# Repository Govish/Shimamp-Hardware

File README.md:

# Shimamp-Hardware
 Hardware Design Files for high-efficiency shim amplifier

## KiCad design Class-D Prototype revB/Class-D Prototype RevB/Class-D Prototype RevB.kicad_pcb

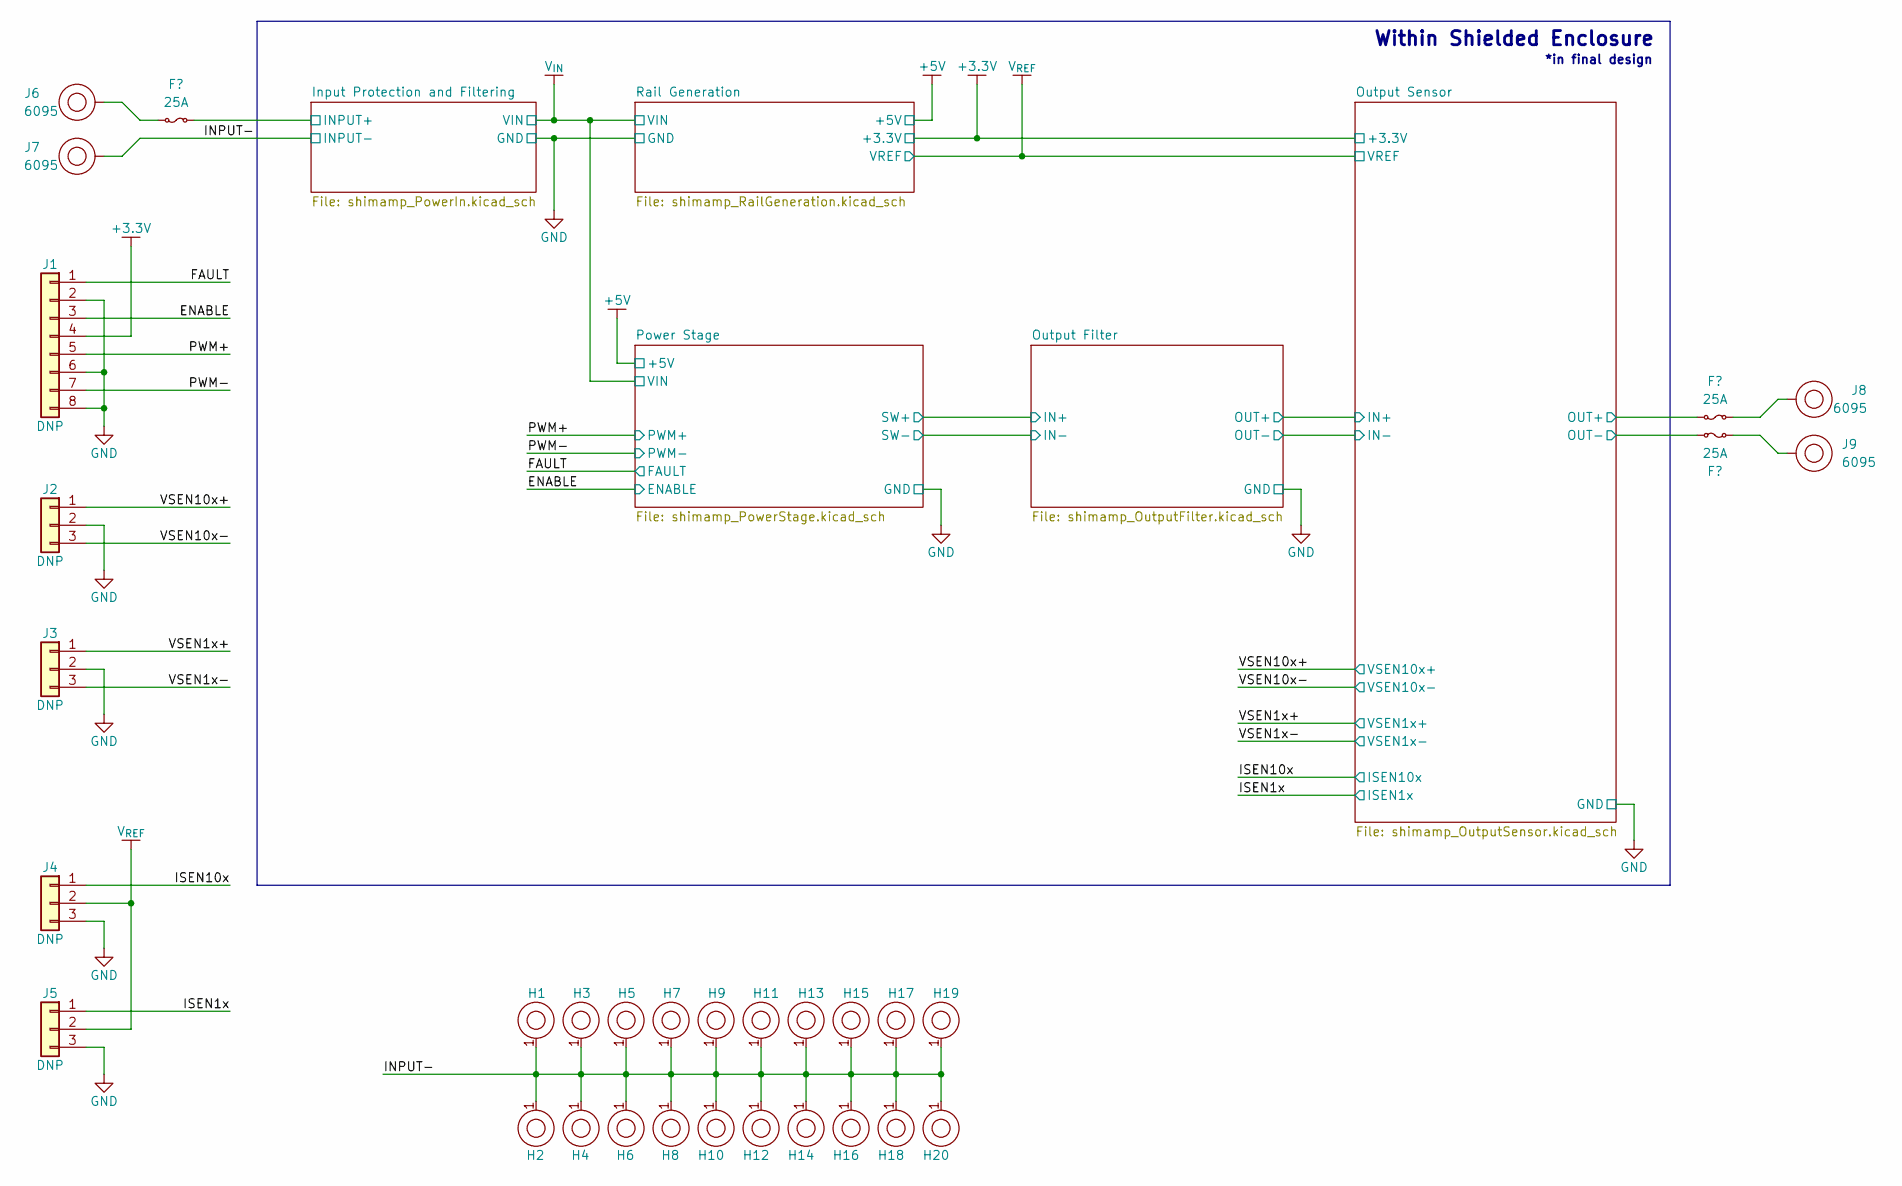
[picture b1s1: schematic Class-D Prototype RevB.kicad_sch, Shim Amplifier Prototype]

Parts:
F1, F2, F3: 25A; Fuse_1206_3216Metric_Pad1.42x1.75mm_HandSolder; Part Number 0685H9250-01
H1, H2, H3, H4, H5, H6, H7, H8, H9, H10, H11, H12, H13, H14, H15, H16, H17, H18, H19, H20: MountingHole-3mm_small_annulus
J1: DNP; PinHeader_1x08_P2.54mm_Vertical
J2, J3, J4, J5: DNP; PinHeader_1x03_P2.54mm_Vertical
J6, J7, J8, J9: 6095; Keystone 6095; Part Number 6095

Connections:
+3.3V: J1.4; also elsewhere on the board
/ENABLE: J1.3; also elsewhere on the board
/FAULT: J1.1; also elsewhere on the board
/INPUT-: H1.1, H2.1, H3.1, H4.1, H5.1, H6.1, H7.1, H8.1, H9.1, H10.1, H11.1, H12.1, H13.1, H14.1, H15.1, H16.1, H17.1, H18.1, H19.1, H20.1, J7.1; also elsewhere on the board
/ISEN1x: J5.1; also elsewhere on the board
/ISEN10x: J4.1; also elsewhere on the board
/Input Protection and Filtering/VIN_ICL+: F1.2; also elsewhere on the board
/Output Sensor/IN-: F3.1; also elsewhere on the board
/Output Sensor/OUT+: F2.1; also elsewhere on the board
/PWM+: J1.5; also elsewhere on the board
/PWM-: J1.7; also elsewhere on the board
/VSEN1x+: J3.1; also elsewhere on the board
/VSEN1x-: J3.3; also elsewhere on the board
/VSEN10x+: J2.1; also elsewhere on the board
/VSEN10x-: J2.3; also elsewhere on the board
GND: J1.2, J1.6, J1.8, J2.2, J3.2, J4.3, J5.3; also elsewhere on the board
unnamed: F1.1, J6.1
unnamed: F2.2, J8.1
unnamed: F3.2, J9.1
V_{REF}: J4.2, J5.2; also elsewhere on the board

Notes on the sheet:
*in final design
Within Shielded Enclosure

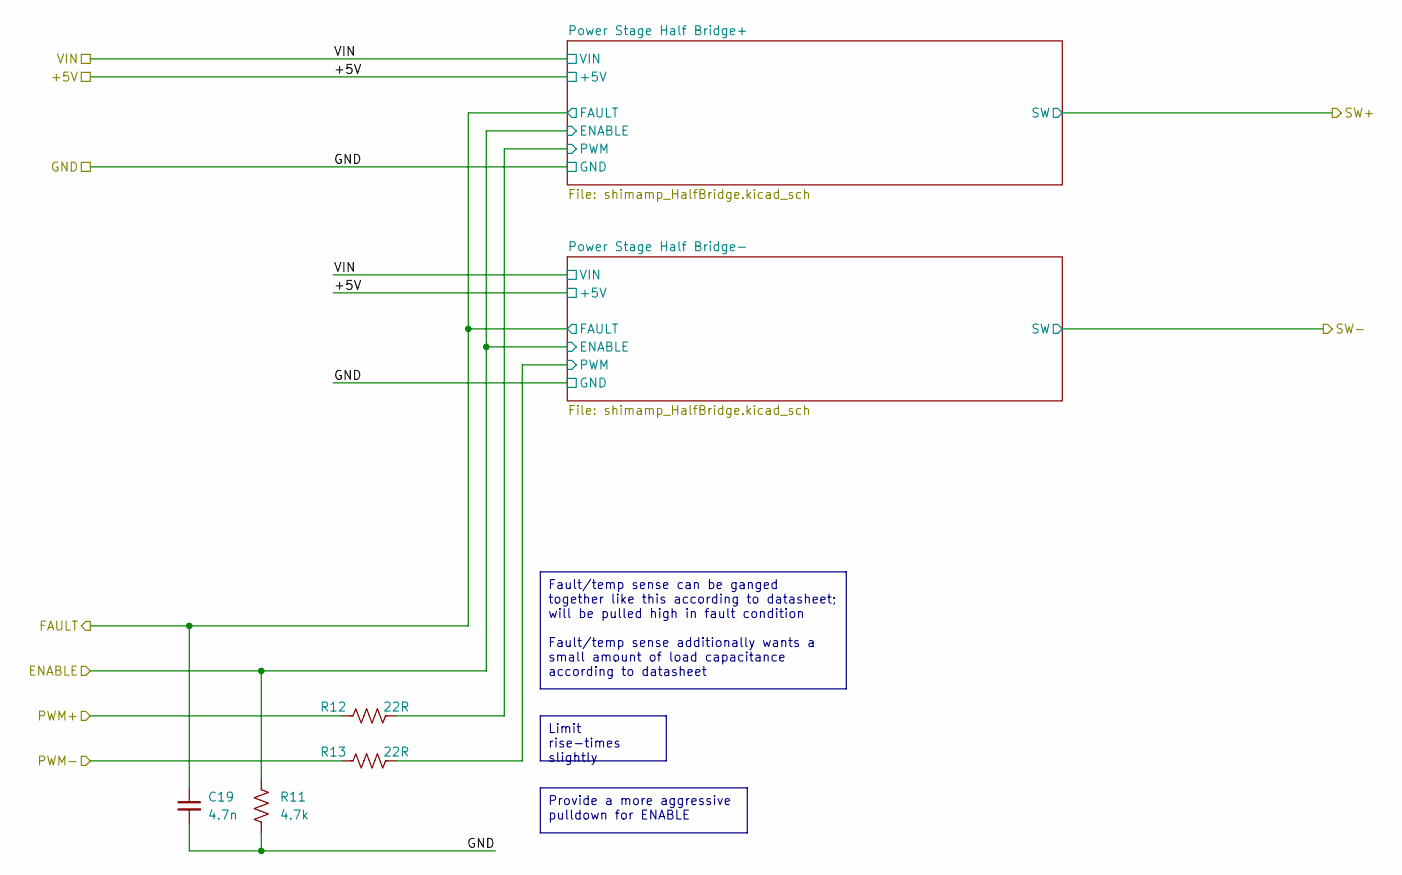
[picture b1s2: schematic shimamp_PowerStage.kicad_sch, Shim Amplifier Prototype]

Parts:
C19: 4.7n; C_0603_1608Metric_Pad1.08x0.95mm_HandSolder; Part Number CL10B472KB8NFNC
R11: 4.7k; R_0603_1608Metric_Pad0.98x0.95mm_HandSolder; Part Number RMCF0603FT4K70
R12, R13: 22R; R_0603_1608Metric_Pad0.98x0.95mm_HandSolder; Part Number RMCF0603FT22R0

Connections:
/ENABLE: R11.2; also elsewhere on the board
/FAULT: C19.1; also elsewhere on the board
/PWM+: R12.1; also elsewhere on the board
/PWM-: R13.1; also elsewhere on the board
/Power Stage/Power Stage Half Bridge+/PWM: R12.2; also elsewhere on the board
/Power Stage/Power Stage Half Bridge-/PWM: R13.2; also elsewhere on the board
GND: C19.2, R11.1; also elsewhere on the board

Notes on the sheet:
Limit rise-times slightly
Provide a more aggressive pulldown for ENABLE
Fault/temp sense can be ganged together like this according to datasheet; will be pulled high in fault condition Fault/temp sense additionally wants a small amount of load capacitance according to datasheet

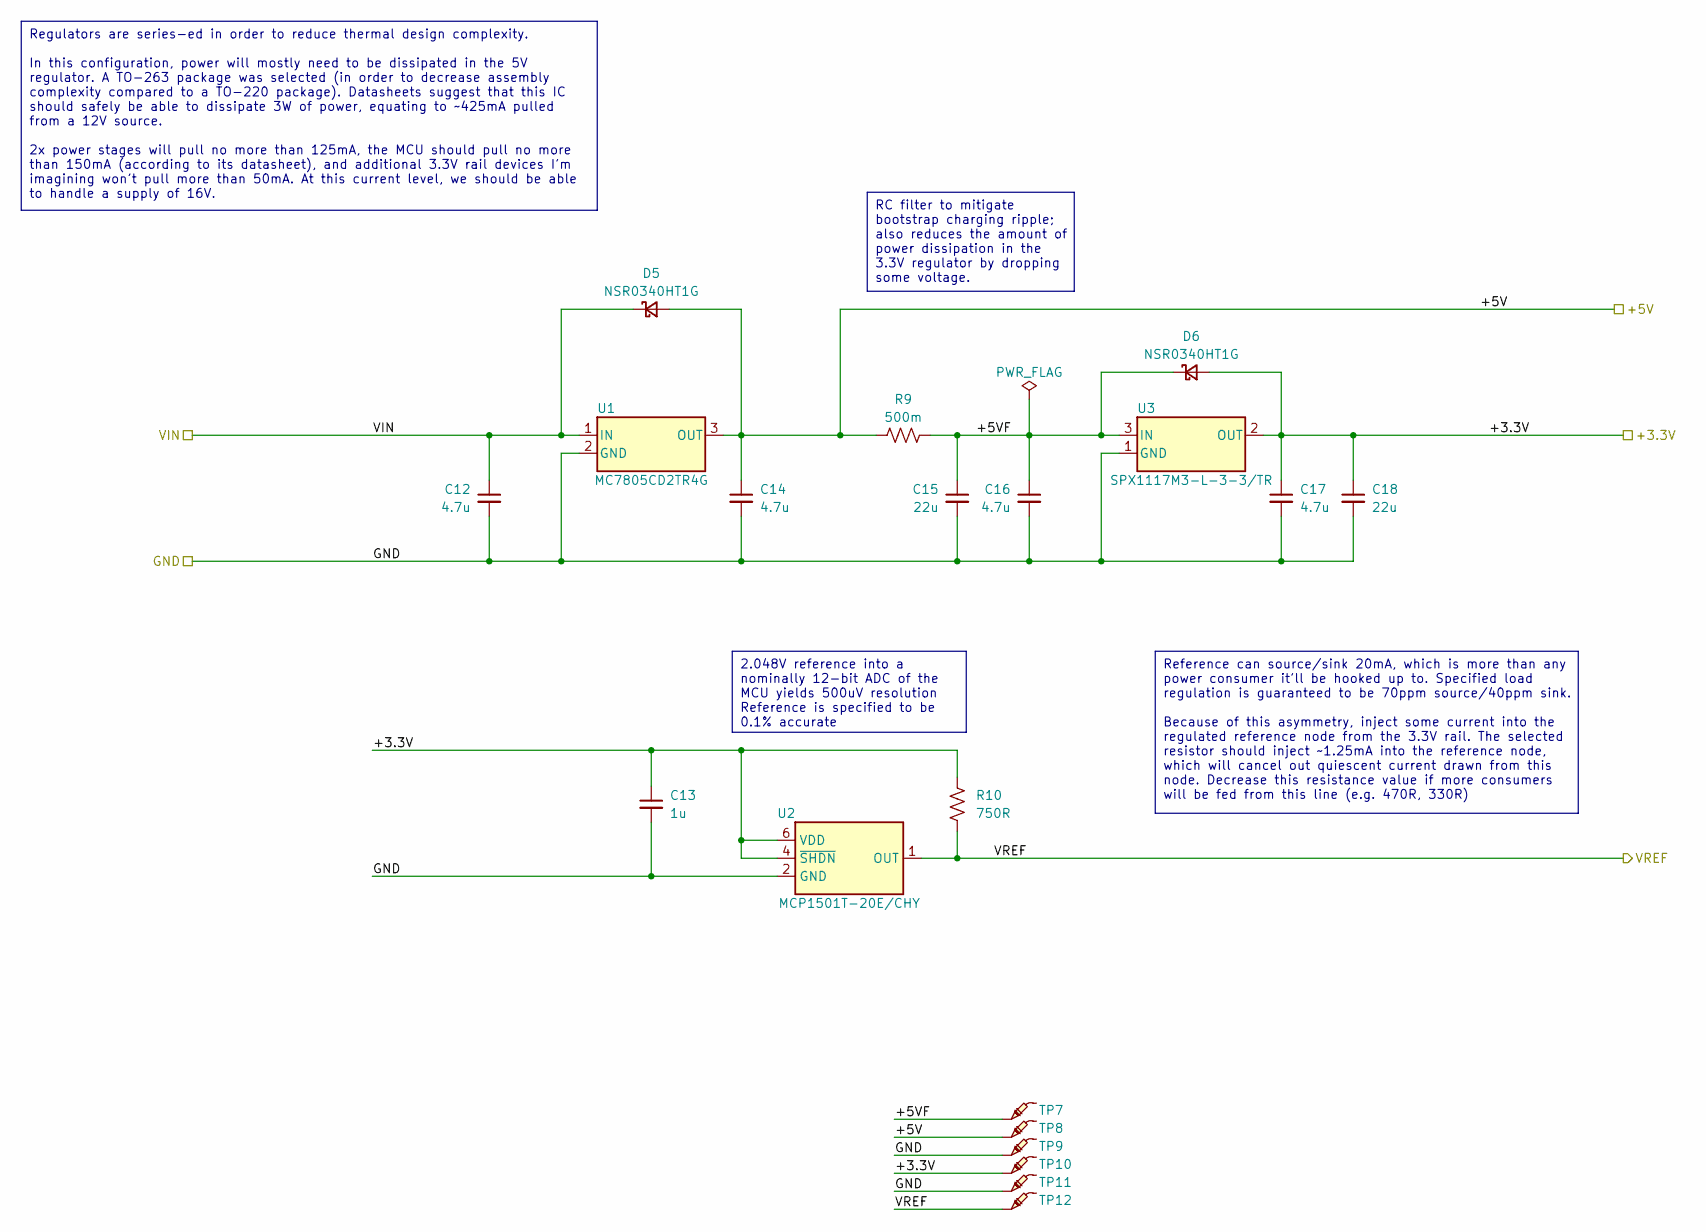
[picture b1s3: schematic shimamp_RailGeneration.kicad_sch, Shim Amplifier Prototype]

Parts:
C12, C14, C16, C17: 4.7u; C_0805_2012Metric_Pad1.18x1.45mm_HandSolder; Part Number CL21A475KLCLQNC
C13: 1u; C_0805_2012Metric_Pad1.18x1.45mm_HandSolder; Part Number CL21B105KBFNNNG
C15, C18: 22u; C_1210_3225Metric_Pad1.33x2.70mm_HandSolder; Part Number CL32B226KAJNNNE
D5, D6: NSR0340HT1G; D_SOD-323_HandSoldering; Part Number NSR0340HT1G
R9: 500m; R_1206_3216Metric_Pad1.30x1.75mm_HandSolder; Part Number CSR1206FKR500
R10: 750R; R_0603_1608Metric_Pad0.98x0.95mm_HandSolder; Part Number RMCF0603FT750R
TP7, TP8, TP9, TP10, TP11, TP12: -; TestPoint_Pad_D2.0mm
U1: MC7805CD2TR4G; TO-263-2; Part Number MC7805CD2TR4G
U2: MCP1501T-20E/CHY; SOT-23-6; Part Number MCP1501T-20E/CHY
U3: SPX1117M3-L-3-3/TR; SOT-223-3_TabPin2; Part Number SPX1117M3-L-3-3/TR

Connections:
+3.3V: C13.1, C17.1, C18.1, D6.2 (A), R10.1, TP10.1, U2.4 (~SHDN), U2.6 (VDD), U3.2 (OUT); also elsewhere on the board
+5V: C14.1, D5.2 (A), R9.1, TP8.1, U1.3 (OUT); also elsewhere on the board
/Rail Generation/+5VF: C15.1, C16.1, D6.1 (K), R9.2, TP7.1, U3.3 (IN)
GND: C12.2, C13.2, C14.2, C15.2, C16.2, C17.2, C18.2, TP9.1, TP11.1, U1.2 (GND), U2.2 (GND), U2.3 (GND), U2.5 (GND), U3.1 (GND); also elsewhere on the board
V_{IN}: C12.1, D5.1 (K), U1.1 (IN); also elsewhere on the board
V_{REF}: R10.2, TP12.1, U2.1 (OUT); also elsewhere on the board

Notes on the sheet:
Regulators are series-ed in order to reduce thermal design complexity. In this configuration, power will mostly need to be dissipated in the 5V regulator. A TO-263 package was selected (in order to decrease assembly complexity compared to a TO-220 package). Datasheets suggest that this IC should sa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
2.048V reference into a nominally 12-bit ADC of the MCU yields 500uV resolution Reference is specified to be 0.1% accurate
Reference can source/sink 20mA, which is more than any power consumer it'll be hooked up to. Specified load regulation is guaranteed to be 70ppm source/40ppm sink. Because of this asymmetry, inject some current into the regulated reference node from the 3.3V rail. The selected resistor should injec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
RC filter to mitigate bootstrap charging ripple; also reduces the amount of power dissipation in the 3.3V regulator by dropping some voltage.

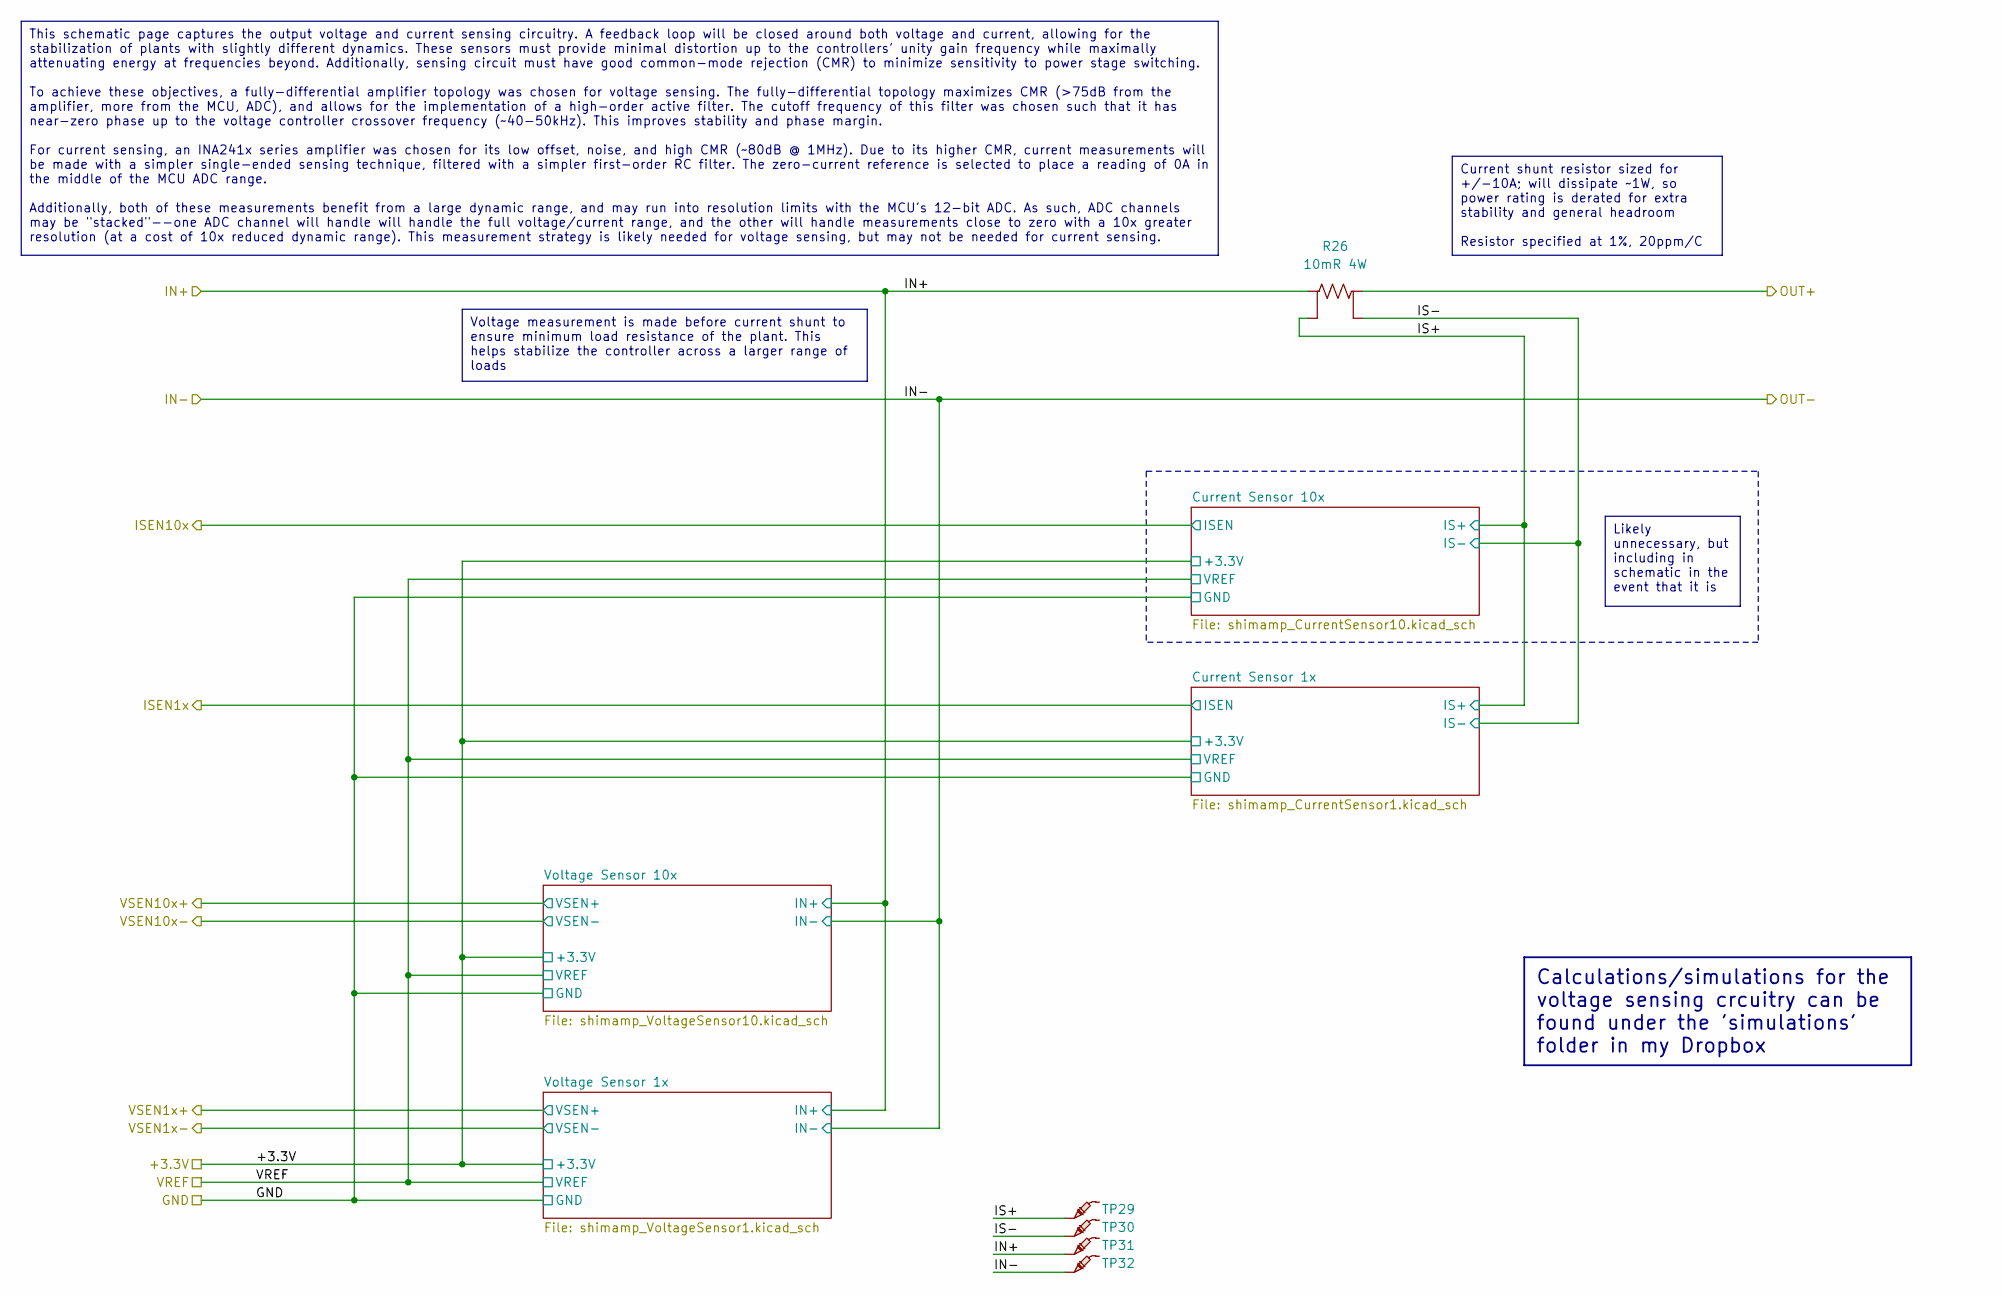
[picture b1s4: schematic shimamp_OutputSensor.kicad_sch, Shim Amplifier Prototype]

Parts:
R26: 10mR 4W; R_2512_6332_CURRENT_SHUNT; Part Number VMS-R010-1.0-U
TP29, TP30, TP31, TP32: -; TestPoint_Pad_D2.0mm

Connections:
/Output Sensor/IN+: R26.2, TP31.1; also elsewhere on the board
/Output Sensor/IN-: TP32.1; also elsewhere on the board
/Output Sensor/IS+: R26.4, TP29.1; also elsewhere on the board
/Output Sensor/IS-: R26.3, TP30.1; also elsewhere on the board
/Output Sensor/OUT+: R26.1; also elsewhere on the board

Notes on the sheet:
This schematic page captures the output voltage and current sensing circuitry. A feedback loop will be closed around both voltage and current, allowing for the stabilization of plants with slightly different dynamics. These sensors must provide minimal distortion up to the controllers' unity gain f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
Calculations/simulations for the voltage sensing crcuitry can be found under the 'simulations' folder in my Dropbox
Likely unnecessary, but including in schematic in the event that it is
Voltage measurement is made before current shunt to ensure minimum load resistance of the plant. This helps stabilize the controller across a larger range of loads
Current shunt resistor sized for +/-10A; will dissipate ~1W, so power rating is derated for extra stability and general headroom Resistor specified at 1%, 20ppm/C

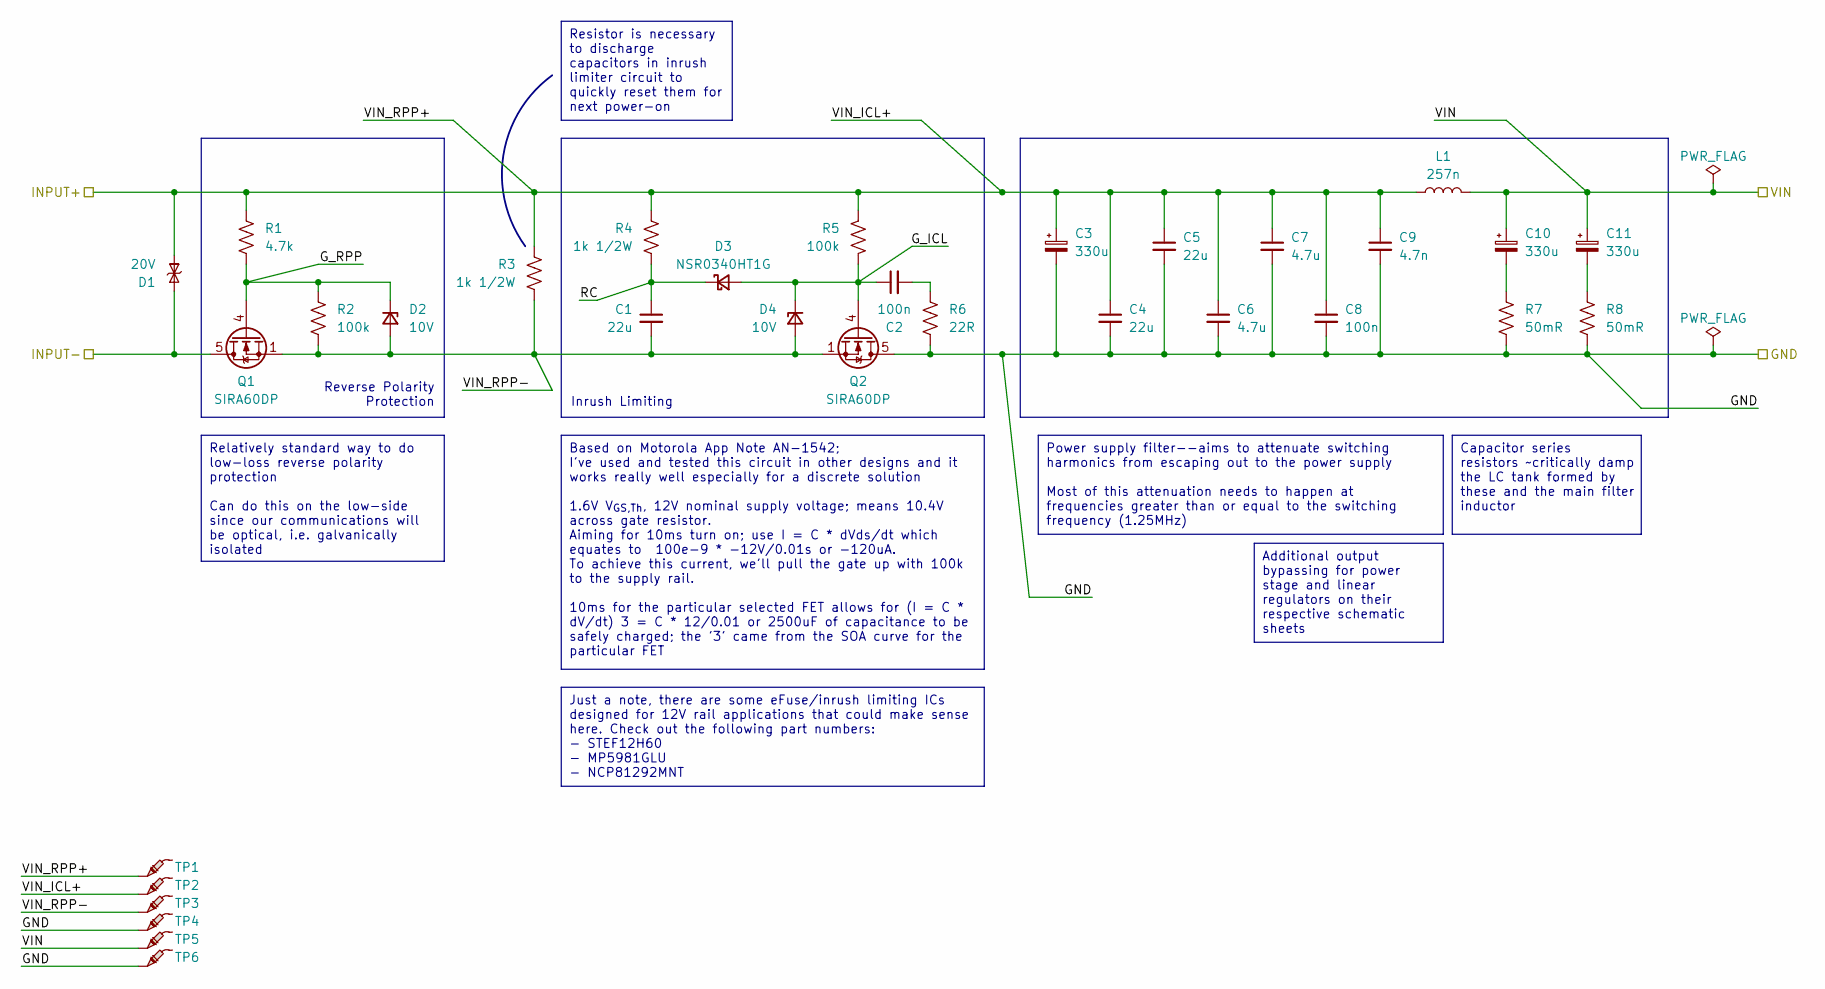
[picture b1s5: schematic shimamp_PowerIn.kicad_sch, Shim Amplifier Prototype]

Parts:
C1, C4, C5: 22u; C_1210_3225Metric_Pad1.33x2.70mm_HandSolder; Part Number CL32B226KAJNNNE
C2, C8: 100n; C_0603_1608Metric_Pad1.08x0.95mm_HandSolder; Part Number CL10B104KB8NNWC
C3, C10, C11: 330u; CP_Elec_10x12.6; Part Number 25SVPF330M
C6, C7: 4.7u; C_0805_2012Metric_Pad1.18x1.45mm_HandSolder; Part Number CL21A475KLCLQNC
C9: 4.7n; C_0603_1608Metric_Pad1.08x0.95mm_HandSolder; Part Number CL10B472KB8NFNC
D1: 20V; D_SMC; Part Number SMCJ20CA
D2, D4: 10V; D_SOD-323_HandSoldering; Part Number MM3Z10VC
D3: NSR0340HT1G; D_SOD-323_HandSoldering; Part Number NSR0340HT1G
L1: 257n; COILCRAFT_2014; Part Number 2014VS-251MED
Q1, Q2: SIRA60DP; PQFN-8-EP_6x5mm_P1.27mm_Generic; Part Number SIRA60DP-T1-GE3
R1: 4.7k; R_0603_1608Metric_Pad0.98x0.95mm_HandSolder; Part Number RMCF0603FT4K70
R2, R5: 100k; R_0603_1608Metric_Pad0.98x0.95mm_HandSolder; Part Number RMCF0603FT100K
R3, R4: 1k 1/2W; R_1210_3225Metric_Pad1.30x2.65mm_HandSolder; Part Number RMCF1210JT1K00
R6: 22R; R_0603_1608Metric_Pad0.98x0.95mm_HandSolder; Part Number RMCF0603FT22R0
R7, R8: 50mR; R_2512_6332Metric_Pad1.40x3.35mm_HandSolder; Part Number CSRN2512FK50L0
TP1, TP2, TP3, TP4, TP5, TP6: -; TestPoint_Pad_D2.0mm

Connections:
/INPUT-: D1.2 (A), Q1.5 (D); also elsewhere on the board
/Input Protection and Filtering/G_ICL: C2.1, D3.2 (A), D4.1 (K), Q2.4 (G), R5.2
/Input Protection and Filtering/G_RPP: D2.1 (K), Q1.4 (G), R1.2, R2.1
/Input Protection and Filtering/RC: C1.1, D3.1 (K), R4.2
/Input Protection and Filtering/VIN_ICL+: C3.1, C4.1, C5.1, C6.1, C7.1, C8.1, C9.1, D1.1 (K), L1.1, R1.1, R3.1, R4.1, R5.1, TP1.1, TP2.1; also elsewhere on the board
/Input Protection and Filtering/VIN_RPP-: C1.2, D2.2 (A), D4.2 (A), Q1.1 (S), Q1.2 (S), Q1.3 (S), Q2.1 (S), Q2.2 (S), Q2.3 (S), R2.2, R3.2, TP3.1
GND: C3.2, C4.2, C5.2, C6.2, C7.2, C8.2, C9.2, Q2.5 (D), R6.2, R7.2, R8.2, TP4.1, TP6.1; also elsewhere on the board
unnamed: C2.2, R6.1
unnamed: C10.2, R7.1
unnamed: C11.2, R8.1
V_{IN}: C10.1, C11.1, L1.2, TP5.1; also elsewhere on the board

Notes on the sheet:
Additional output bypassing for power stage and linear regulators on their respective schematic sheets
Power supply filter--aims to attenuate switching harmonics from escaping out to the power supply Most of this attenuation needs to happen at frequencies greater than or equal to the switching frequency (1.25MHz)
Just a note, there are some eFuse/inrush limiting ICs designed for 12V rail applications that could make sense here. Check out the following part numbers: - STEF12H60 - MP5981GLU - NCP81292MNT
Based on Motorola App Note AN-1542; I've used and tested this circuit in other designs and it works really well especially for a discrete solution 1.6V V_{GS,Th}, 12V nominal supply voltage; means 10.4V across gate resistor. Aiming for 10ms turn on; use I = C * dVds/dt which equates to 100e-9 * -12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
Relatively standard way to do low-loss reverse polarity protection Can do this on the low-side since our communications will be optical, i.e. galvanically isolated
Resistor is necessary to discharge capacitors in inrush limiter circuit to quickly reset them for next power-on
Capacitor series resistors ~critically damp the LC tank formed by these and the main filter inductor
Inrush Limiting
Reverse Polarity Protection

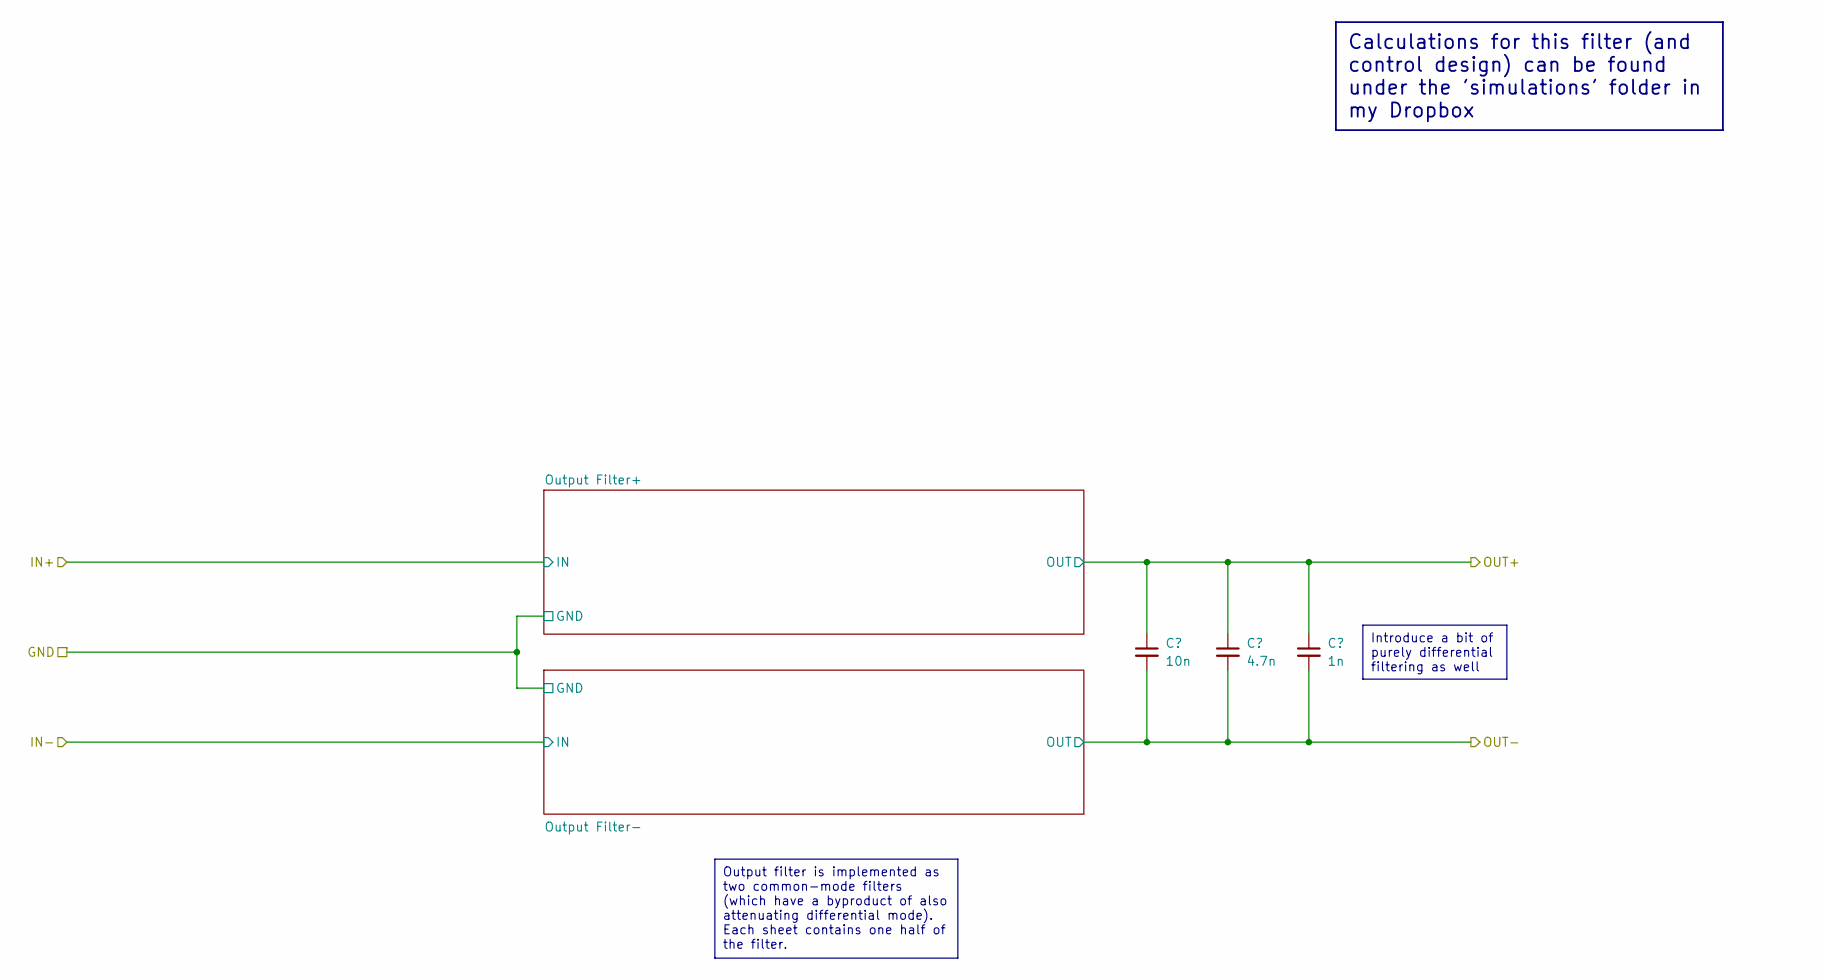
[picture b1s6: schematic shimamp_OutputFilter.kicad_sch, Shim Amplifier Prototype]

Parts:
C66: 10n; C_0603_1608Metric_Pad1.08x0.95mm_HandSolder; Part Number CL10B103KB8NNNC
C67: 4.7n; C_0603_1608Metric_Pad1.08x0.95mm_HandSolder; Part Number CL10B472KB8NFNC
C68: 1n; C_0603_1608Metric_Pad1.08x0.95mm_HandSolder; Part Number CL10B102KB8NNNC

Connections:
/Output Sensor/IN+: C66.1, C67.1, C68.1; also elsewhere on the board
/Output Sensor/IN-: C66.2, C67.2, C68.2; also elsewhere on the board

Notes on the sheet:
Output filter is implemented as two common-mode filters (which have a byproduct of also attenuating differential mode). Each sheet contains one half of the filter.
Calculations for this filter (and control design) can be found under the 'simulations' folder in my Dropbox
Introduce a bit of purely differential filtering as well

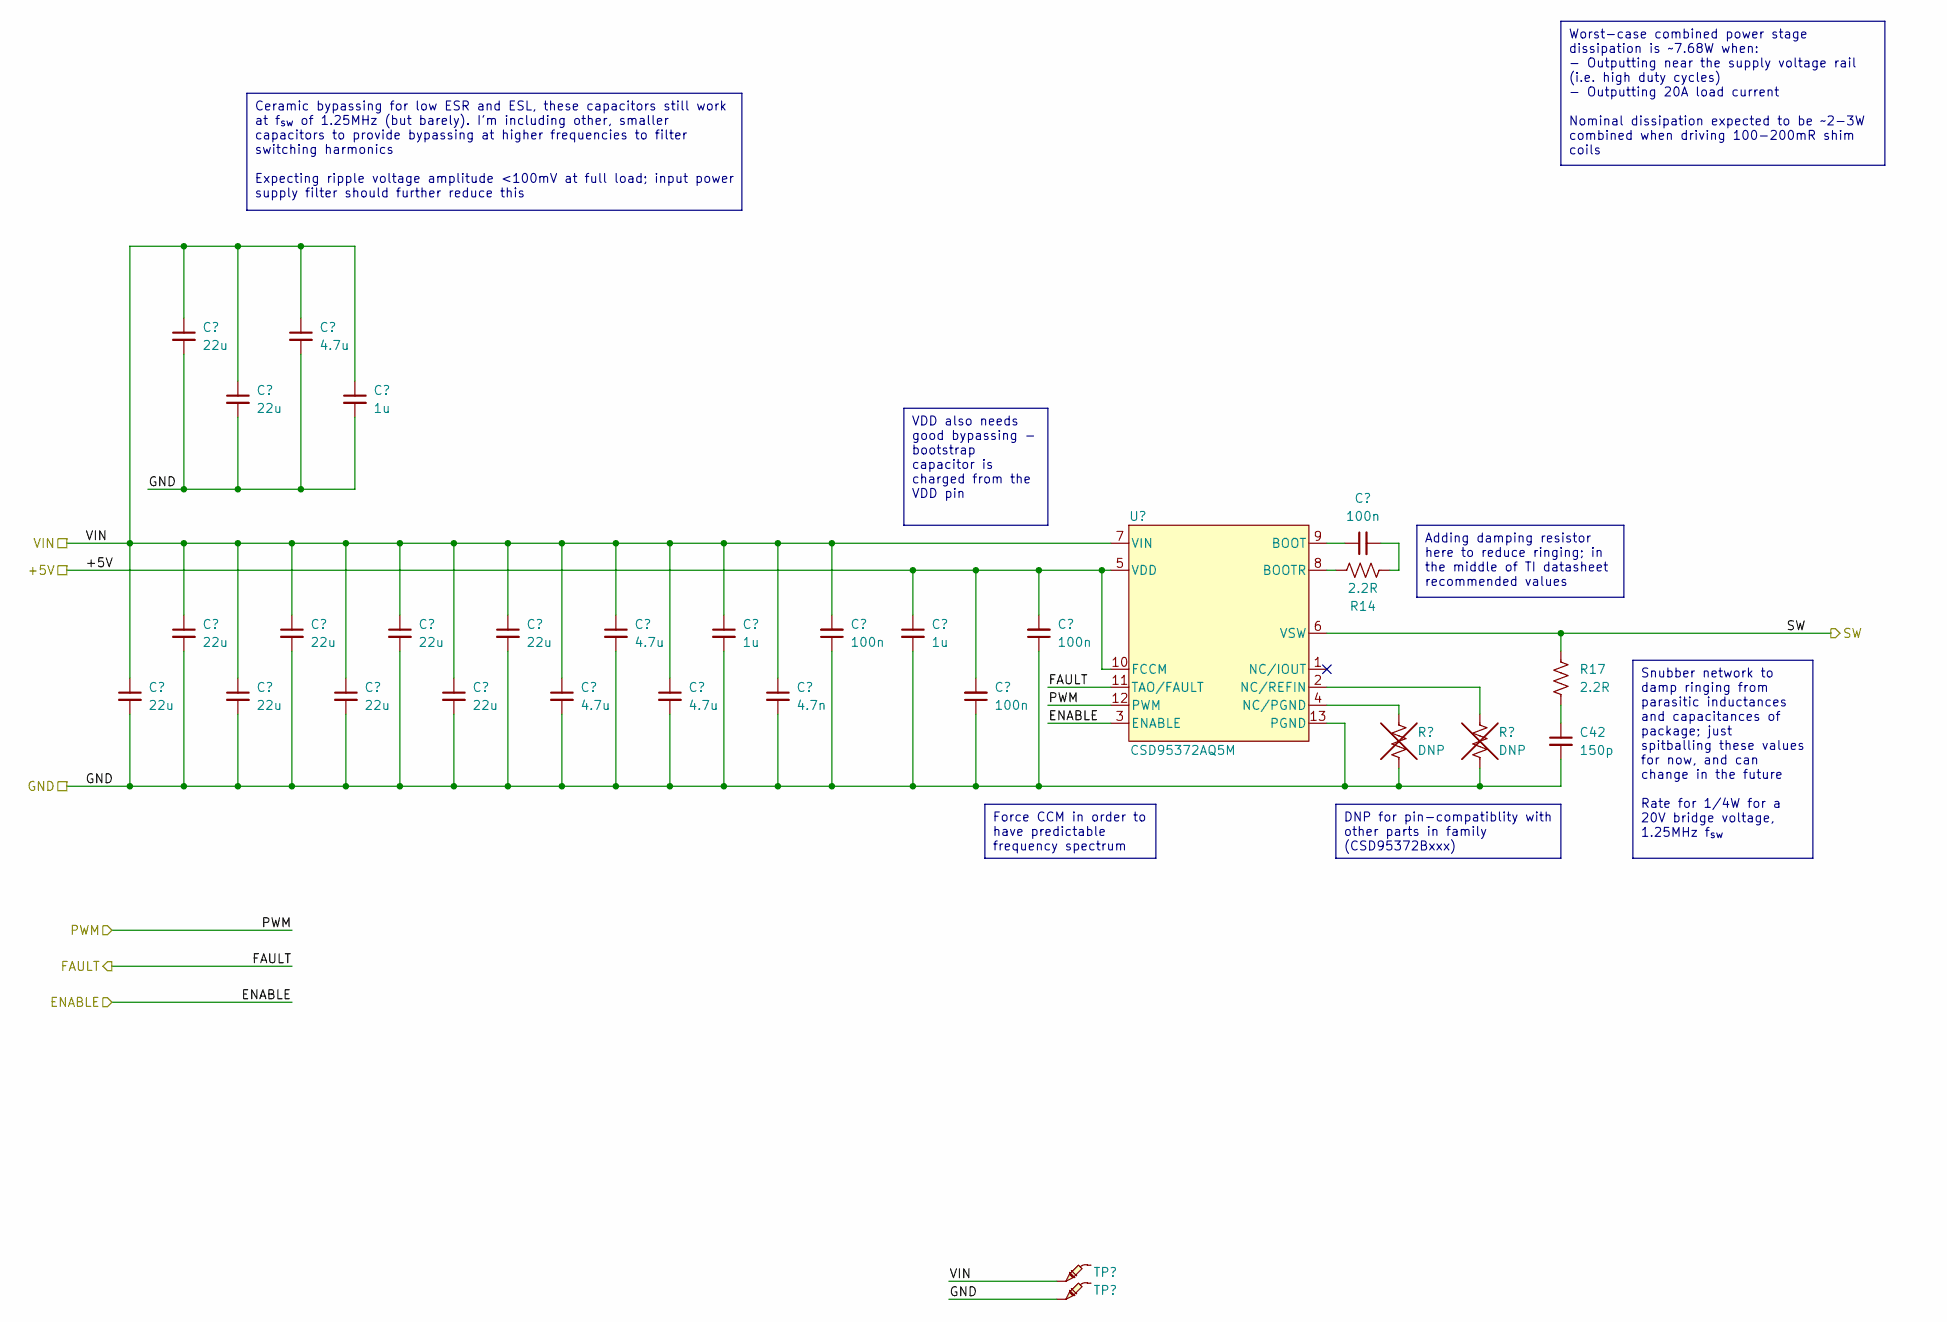
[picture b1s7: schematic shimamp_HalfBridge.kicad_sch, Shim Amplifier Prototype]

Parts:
C20, C21, C22, C23, C24, C25, C27, C29, C30, C31: 22u; C_1210_3225Metric_Pad1.33x2.70mm_HandSolder; Part Number CL32B226KAJNNNE
C26, C32, C33, C34: 4.7u; C_0805_2012Metric_Pad1.18x1.45mm_HandSolder; Part Number CL21A475KLCLQNC
C28, C35, C38: 1u; C_0805_2012Metric_Pad1.18x1.45mm_HandSolder; Part Number CL21B105KBFNNNG
C36: 4.7n; C_0603_1608Metric_Pad1.08x0.95mm_HandSolder; Part Number CL10B472KB8NFNC
C37, C39, C40, C41: 100n; C_0603_1608Metric_Pad1.08x0.95mm_HandSolder; Part Number CL10B104KB8NNWC
C42: 150p; C_0603_1608Metric_Pad1.08x0.95mm_HandSolder; Part Number GCM1885C2A151JA16D
R14, R17: 2.2R; R_0805_2012Metric_Pad1.20x1.40mm_HandSolder; Part Number RPC0805JT2R20-UP
R15, R16: DNP; DNP_R_0603_1608Metric_Pad0.98x0.95mm_HandSolder
TP13, TP14: -; TestPoint_Pad_D2.0mm
U4: CSD95372AQ5M; LSON-12-1EP_5x6mm; Part Number CSD95372AQ5M

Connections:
+5V: C38.1, C39.2, C40.2, U4.5 (VDD), U4.10 (FCCM); also elsewhere on the board
/ENABLE: U4.3 (ENABLE); also elsewhere on the board
/FAULT: U4.11 (TAO/FAULT); also elsewhere on the board
/Power Stage/Power Stage Half Bridge+/PWM: U4.12 (PWM); also elsewhere on the board
/Power Stage/Power Stage Half Bridge+/SW: R17.1, U4.6 (VSW); also elsewhere on the board
GND: C20.2, C21.2, C22.2, C23.2, C24.2, C25.2, C26.2, C27.2, C28.2, C29.2, C30.2, C31.2, C32.2, C33.2, C34.2, C35.2, C36.2, C37.1, C38.2, C39.1, C40.1, C42.2, R15.2, R16.2, TP14.1, U4.13 (PGND); also elsewhere on the board
unnamed: C41.2, R14.2
unnamed: C42.1, R17.2
unnamed: C41.1, U4.9 (BOOT)
unnamed: R14.1, U4.8 (BOOTR)
unnamed: R15.1, U4.4 (NC/PGND)
unnamed: R16.1, U4.2 (NC/REFIN)
V_{IN}: C20.1, C21.1, C22.1, C23.1, C24.1, C25.1, C26.1, C27.1, C28.1, C29.1, C30.1, C31.1, C32.1, C33.1, C34.1, C35.1, C36.1, C37.2, TP13.1, U4.7 (VIN); also elsewhere on the board

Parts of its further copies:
C43, C44, C45, C46, C47, C48, C50, C52, C53, C54: 22u; C_1210_3225Metric_Pad1.33x2.70mm_HandSolder; Part Number CL32B226KAJNNNE
C49, C55, C56, C57: 4.7u; C_0805_2012Metric_Pad1.18x1.45mm_HandSolder; Part Number CL21A475KLCLQNC
C51, C58, C61: 1u; C_0805_2012Metric_Pad1.18x1.45mm_HandSolder; Part Number CL21B105KBFNNNG
C59: 4.7n; C_0603_1608Metric_Pad1.08x0.95mm_HandSolder; Part Number CL10B472KB8NFNC
C60, C62, C63, C64: 100n; C_0603_1608Metric_Pad1.08x0.95mm_HandSolder; Part Number CL10B104KB8NNWC
C65: 150p; C_0603_1608Metric_Pad1.08x0.95mm_HandSolder; Part Number GCM1885C2A151JA16D
R18, R21: 2.2R; R_0805_2012Metric_Pad1.20x1.40mm_HandSolder; Part Number RPC0805JT2R20-UP
R19, R20: DNP; DNP_R_0603_1608Metric_Pad0.98x0.95mm_HandSolder
TP15, TP16: -; TestPoint_Pad_D2.0mm
U5: CSD95372AQ5M; LSON-12-1EP_5x6mm; Part Number CSD95372AQ5M

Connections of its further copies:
+5V: C61.1, C62.2, C63.2, U5.5 (VDD), U5.10 (FCCM); also elsewhere on the board
/ENABLE: U5.3 (ENABLE); also elsewhere on the board
/FAULT: U5.11 (TAO/FAULT); also elsewhere on the board
/Power Stage/Power Stage Half Bridge-/PWM: U5.12 (PWM); also elsewhere on the board
/Power Stage/Power Stage Half Bridge-/SW: R21.1, U5.6 (VSW); also elsewhere on the board
GND: C43.2, C44.2, C45.2, C46.2, C47.2, C48.2, C49.2, C50.2, C51.2, C52.2, C53.2, C54.2, C55.2, C56.2, C57.2, C58.2, C59.2, C60.1, C61.2, C62.1, C63.1, C65.2, R19.2, R20.2, TP16.1, U5.13 (PGND); also elsewhere on the board
unnamed: C64.2, R18.2
unnamed: C65.1, R21.2
unnamed: C64.1, U5.9 (BOOT)
unnamed: R18.1, U5.8 (BOOTR)
unnamed: R19.1, U5.4 (NC/PGND)
unnamed: R20.1, U5.2 (NC/REFIN)
V_{IN}: C43.1, C44.1, C45.1, C46.1, C47.1, C48.1, C49.1, C50.1, C51.1, C52.1, C53.1, C54.1, C55.1, C56.1, C57.1, C58.1, C59.1, C60.2, TP15.1, U5.7 (VIN); also elsewhere on the board

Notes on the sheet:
Worst-case combined power stage dissipation is ~7.68W when: - Outputting near the supply voltage rail (i.e. high duty cycles) - Outputting 20A load current Nominal dissipation expected to be ~2-3W combined when driving 100-200mR shim coils
Adding damping resistor here to reduce ringing; in the middle of TI datasheet recommended values
VDD also needs good bypassing - bootstrap capacitor is charged from the VDD pin
DNP for pin-compatiblity with other parts in family (CSD95372Bxxx)
Force CCM in order to have predictable frequency spectrum
Ceramic bypassing for low ESR and ESL, these capacitors still work at f_{sw} of 1.25MHz (but barely). I'm including other, smaller capacitors to provide bypassing at higher frequencies to filter switching harmonics Expecting ripple voltage amplitude <100mV at full load; input power supply filter sh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
Snubber network to damp ringing from parasitic inductances and capacitances of package; just spitballing these values for now, and can change in the future Rate for 1/4W for a 20V bridge voltage, 1.25MHz f_{sw}
